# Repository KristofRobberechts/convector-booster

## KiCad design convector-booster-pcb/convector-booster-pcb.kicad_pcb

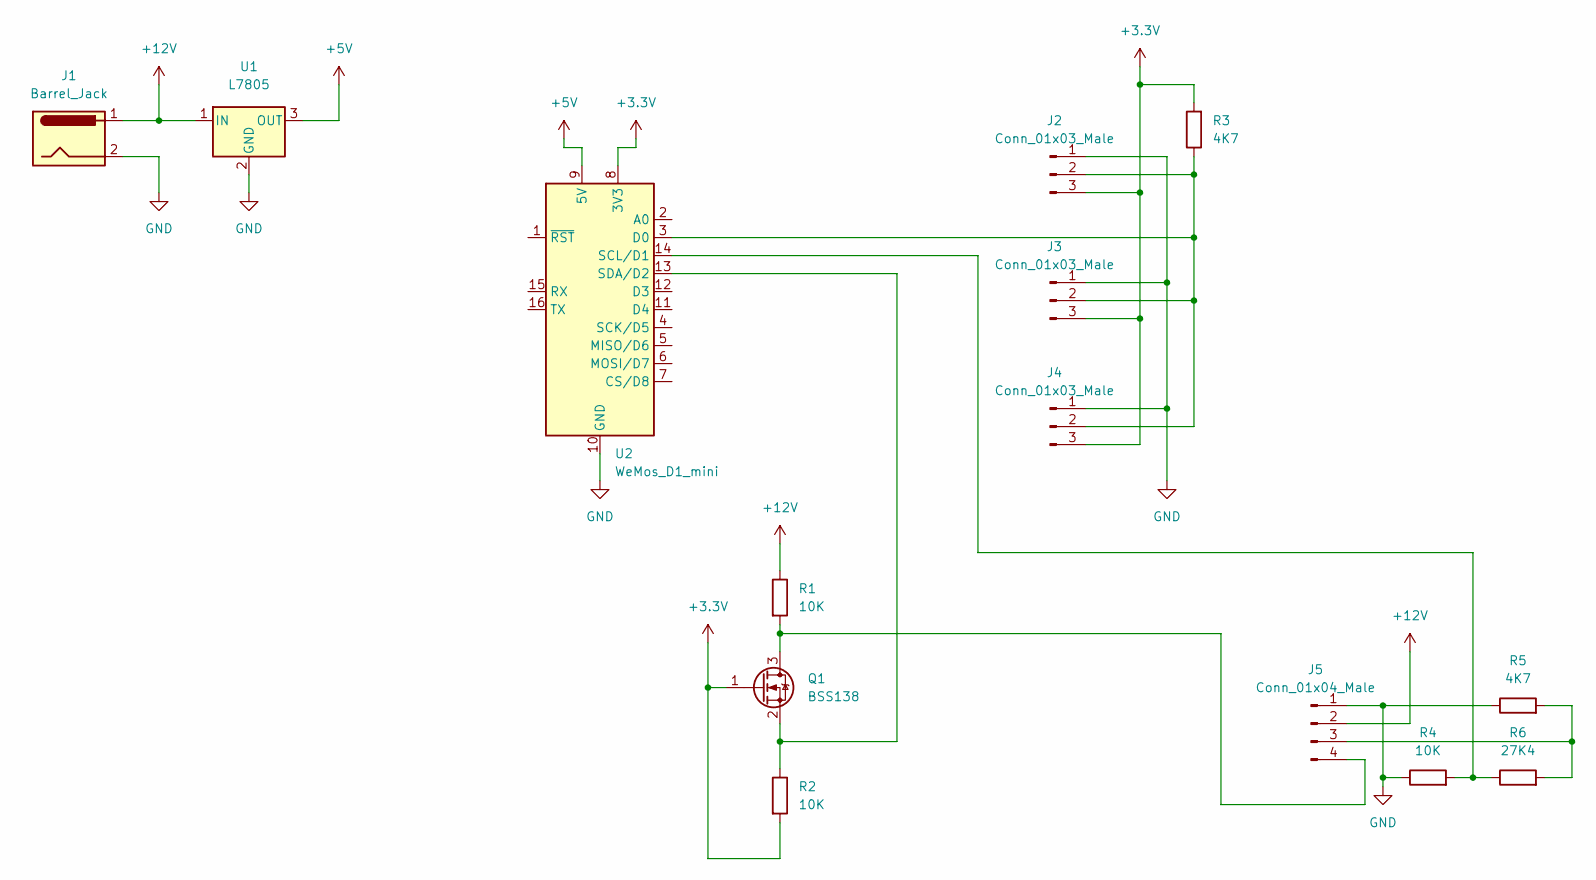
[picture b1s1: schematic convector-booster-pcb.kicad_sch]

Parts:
J1: Barrel_Jack; BarrelJack_GCT_DCJ200-10-A_Horizontal
J2, J3, J4: Conn_01x03_Male; JST_XH_B3B-XH-A_1x03_P2.50mm_Vertical
J5: Conn_01x04_Male; PinHeader_1x04_P2.54mm_Vertical
Q1: BSS138; SOT-23
R1, R2, R4: 10K; R_1206_3216Metric_Pad1.30x1.75mm_HandSolder
R3, R5: 4K7; R_1206_3216Metric_Pad1.30x1.75mm_HandSolder
R6: 27K4; R_1206_3216Metric_Pad1.30x1.75mm_HandSolder
U1: L7805; TO-220-3_Vertical
U2: WeMos_D1_mini; WEMOS_D1_mini_light

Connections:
+3V3: J2.3, J3.3, J4.3, Q1.1 (G), R2.2, R3.2, U2.8 (3V3)
+5V: U1.3 (OUT), U2.9 (5V)
+12V: J1.1, J5.2, R1.1, U1.1 (IN)
GND: J1.2, J2.1, J3.1, J4.1, J5.1, R4.1, R5.1, U1.2 (GND), U2.10 (GND)
unnamed: J2.2, J3.2, J4.2, R3.1, U2.3 (D0)
unnamed: J5.3, R5.2, R6.2
unnamed: J5.4, Q1.3 (D), R1.2
unnamed: Q1.2 (S), R2.1, U2.13 (SDA/D2)
unnamed: R4.2, R6.1, U2.14 (SCL/D1)

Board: 2 copper layers, 14 parts (0 on the bottom side), 9 nets, no tracks yet.

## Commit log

2022-01-08 Added KiCad files.
2022-01-08 Updated KiCad files.
